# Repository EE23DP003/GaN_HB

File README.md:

# GaN_HB
Infineon GaN Half Bridge board design for validating PWM schemes using CHB grid connected inverter

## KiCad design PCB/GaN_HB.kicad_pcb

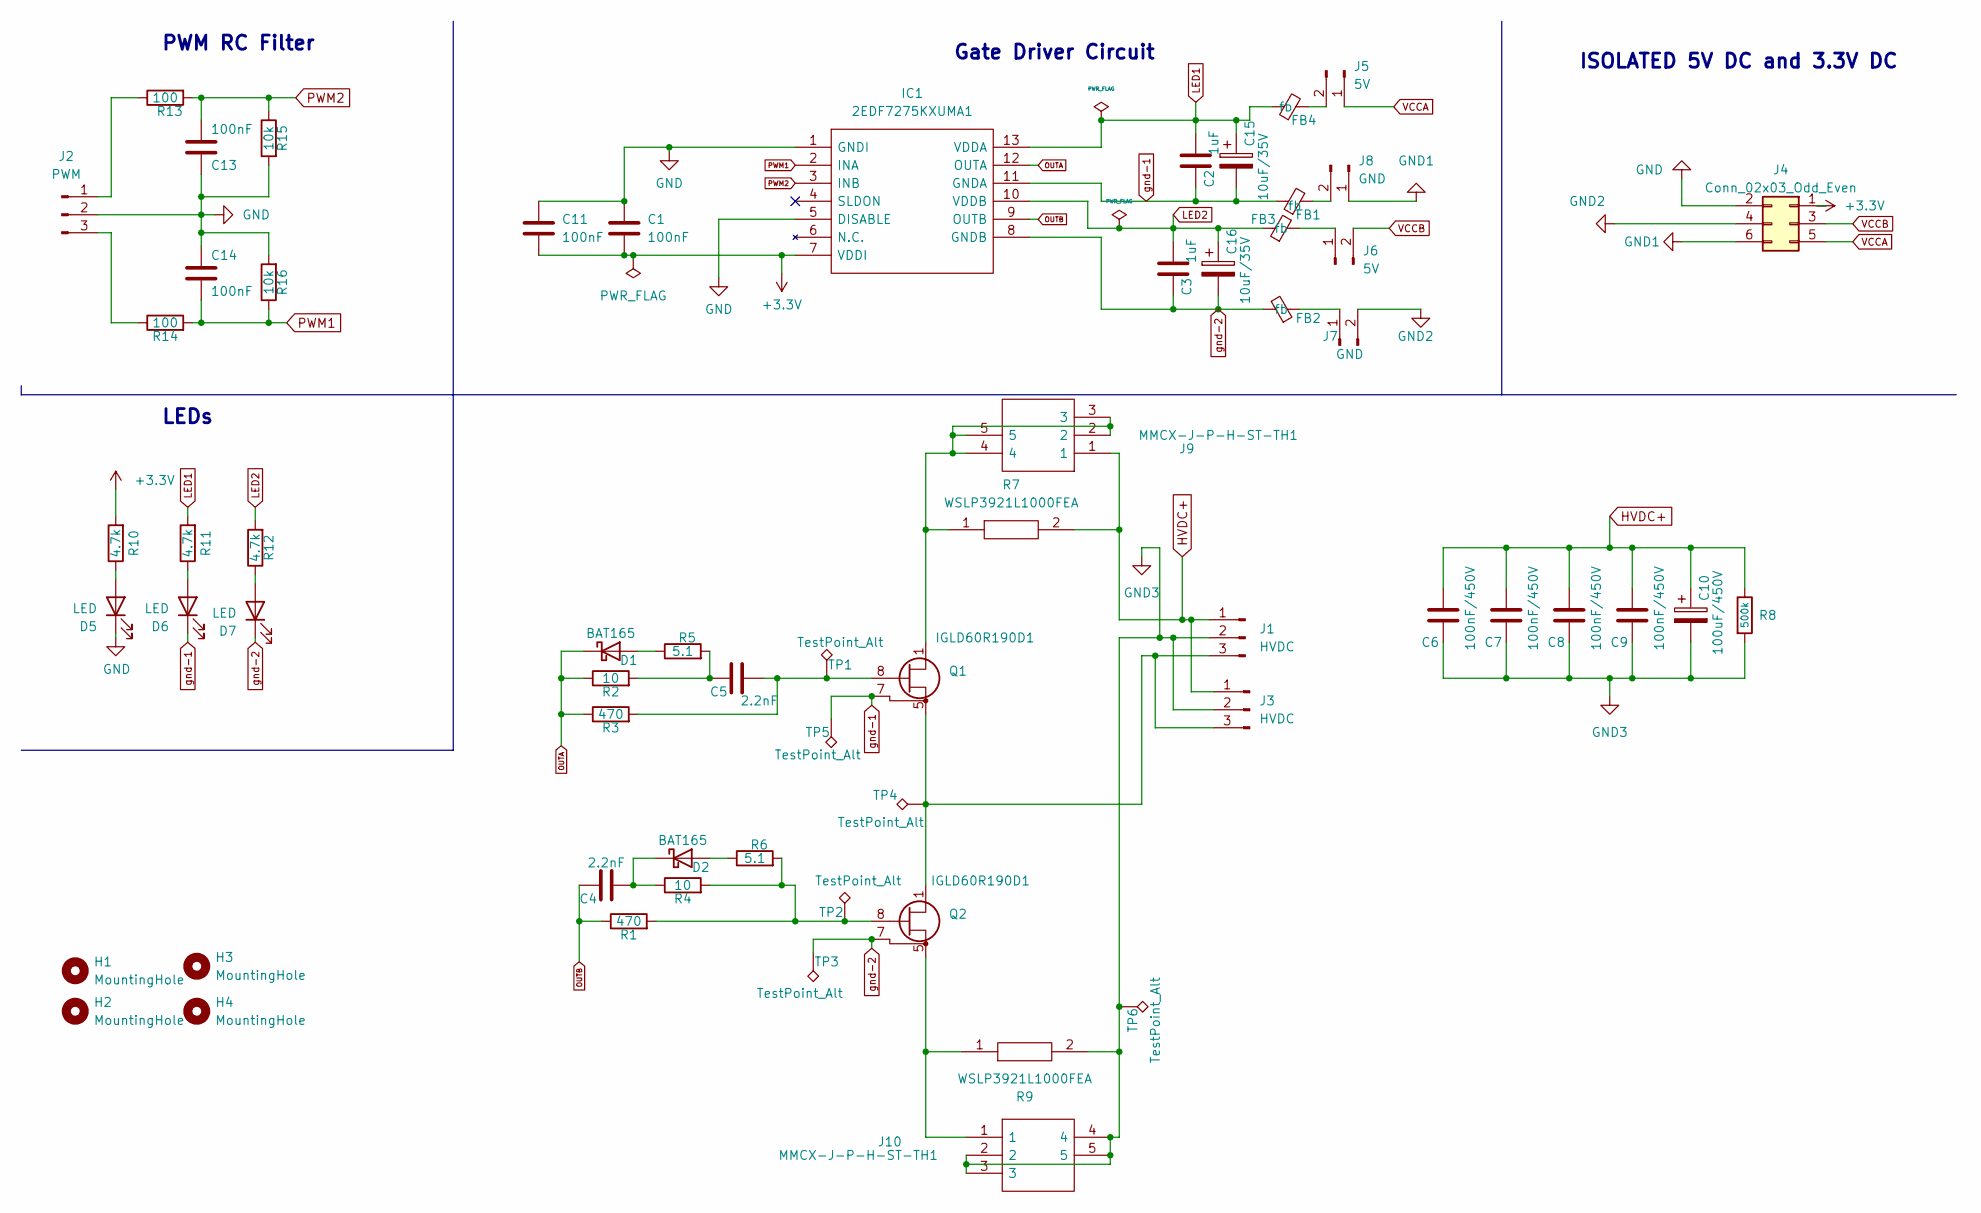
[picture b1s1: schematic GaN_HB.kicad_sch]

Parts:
C1, C11, C13, C14: 100nF; C_0805_2012Metric
C2, C3: 1uF; C_0805_2012Metric
C4, C5: 2.2nF; C_0805_2012Metric
C6, C7, C8, C9: 100nF/450V; C_1206_3216Metric
C10: 100uF/450V; CAPPRD750W80D1825H3200
C15, C16: 10uF/35V; CP_Elec_5x5.3
D1, D2: BAT165; D_SOD-323
D5, D6, D7: LED; LED_0805_2012Metric
FB1, FB2, FB3, FB4: fb; R_0805_2012Metric
H1, H2, H3, H4: MountingHole; MountingHole_3.2mm_M3
IC1: 2EDF7275KXUMA1; TFLGA65P500X500X106-14_13N-V; Mouser Part Number 726-2EDF7275KXUMA1
J1, J3: HVDC; Molex_KK-396_A-41791-0003_1x03_P3.96mm_Vertical
J2: PWM; Molex_KK-254_AE-6410-03A_1x03_P2.54mm_Vertical
J4: Conn_02x03_Odd_Even; PinSocket_2x03_P2.54mm_Horizontal
J5, J6: 5V; PinHeader_1x02_P2.54mm_Vertical
J7, J8: GND; PinHeader_1x02_P2.54mm_Vertical
J9, J10: MMCX-J-P-H-ST-TH1; MMCXJPHSTTH1; Mouser Part Number 200-MMCXJPHSTTH1
Q1, Q2: IGLD60R190D1; Infineon_PG-LSON-8-1
R1, R3: 470; R_0805_2012Metric
R2, R4: 10; R_0805_2012Metric
R5, R6: 5.1; R_0805_2012Metric
R7, R9: WSLP3921L1000FEA; RESC10052X50N; Manufacturer_Part_Number WSLP3921L1000FEA; Mouser Part Number 71-WSLP3921L1000FEA
R8: 500k; R_0805_2012Metric
R10, R11, R12: 4.7k; R_0805_2012Metric
R13, R14: 100; R_0805_2012Metric
R15, R16: 10k; R_0805_2012Metric
TP1, TP2, TP3, TP4, TP5, TP6: TestPoint_Alt; TestPoint_Keystone_5000-5004_Miniature

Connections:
+3.3V: C1.2, C11.2, IC1.7 (VDDI), J4.1, R10.2
GND: C1.1, C11.1, C13.1, C14.1, D5.1 (K), IC1.1 (GNDI), IC1.5 (DISABLE), J2.2, J4.2, R15.2, R16.2
GND1: J4.6, J8.1
GND2: J4.4, J7.2
GND3: C6.2, C7.2, C8.2, C9.2, C10.2, J1.2, J3.2, J10.2, J10.3, J10.4, J10.5, R8.2, R9.2, TP6.1
HVDC+: C6.1, C7.1, C8.1, C9.1, C10.1, J1.1, J3.1, J9.1, R7.2, R8.1
LED1: C2.2, C15.1, FB4.1, IC1.13 (VDDA), R11.2
LED2: C3.2, C16.1, FB3.1, IC1.10 (VDDB), R12.2
unnamed: C5.1, R2.2, R5.2
unnamed: D1.2 (A), R5.1
unnamed: D2.2 (A), R6.1
unnamed: C4.2, D2.1 (K), R4.1
unnamed: D5.2 (A), R10.1
unnamed: D6.2 (A), R11.1
unnamed: D7.2 (A), R12.1
unnamed: J1.3, J3.3, Q1.5 (S), Q1.6 (S), Q1.9 (S), Q2.1 (D), Q2.2 (D), Q2.3 (D), Q2.4 (D), TP4.1
unnamed: J2.1, R13.1
unnamed: J2.3, R14.1
unnamed: FB4.2, J5.2
unnamed: FB3.2, J6.1
unnamed: FB2.1, J7.1
unnamed: FB1.2, J8.2
unnamed: J9.2, J9.3, J9.4, J9.5, Q1.1 (D), Q1.2 (D), Q1.3 (D), Q1.4 (D), R7.1
unnamed: J10.1, Q2.5 (S), Q2.6 (S), Q2.9 (S), R9.1
unnamed: C5.2, Q1.8 (G), R3.2, TP1.1
unnamed: Q2.8 (G), R1.2, R4.2, R6.2, TP2.1
OUTA: D1.1 (K), IC1.12 (OUTA), R2.1, R3.1
OUTB: C4.1, IC1.9 (OUTB), R1.1
PWM1: C14.2, IC1.2 (INA), R14.2, R16.1
PWM2: C13.2, IC1.3 (INB), R13.2, R15.1
VCCA: J4.5, J5.1
VCCB: J4.3, J6.2
gnd-1: C2.1, C15.2, D6.1 (K), FB1.1, IC1.11 (GNDA), Q1.7 (SS), TP5.1
gnd-2: C3.1, C16.2, D7.1 (K), FB2.2, IC1.8 (GNDB), Q2.7 (SS), TP3.1

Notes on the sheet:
LEDs
ISOLATED 5V DC and 3.3V DC
PWM RC Filter
Gate Driver Circuit

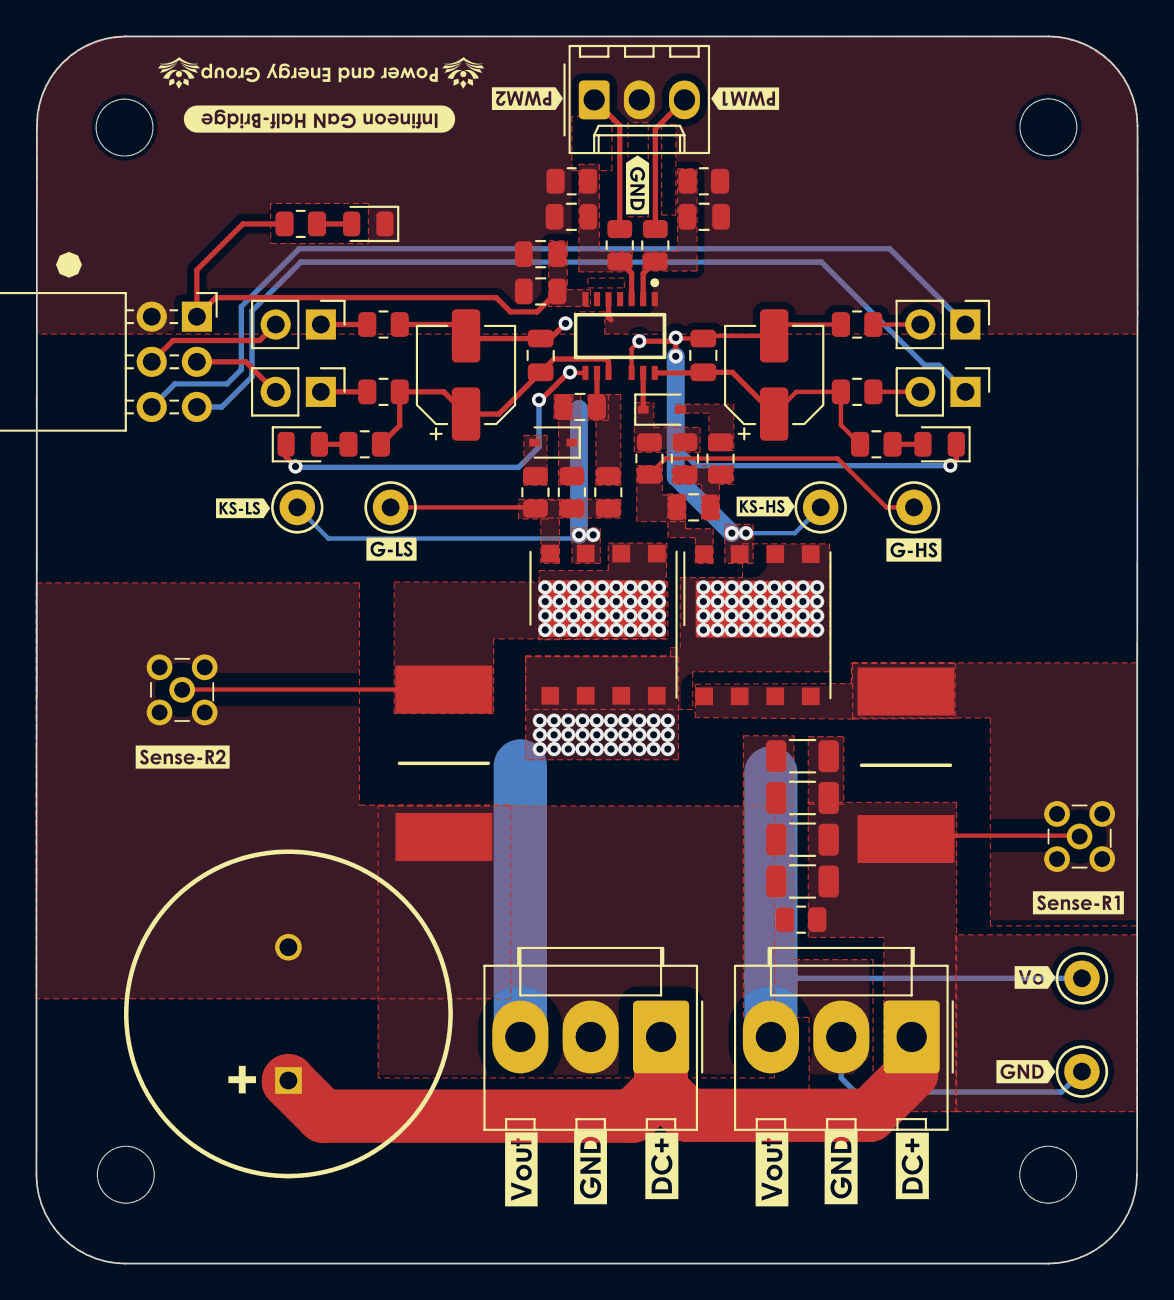
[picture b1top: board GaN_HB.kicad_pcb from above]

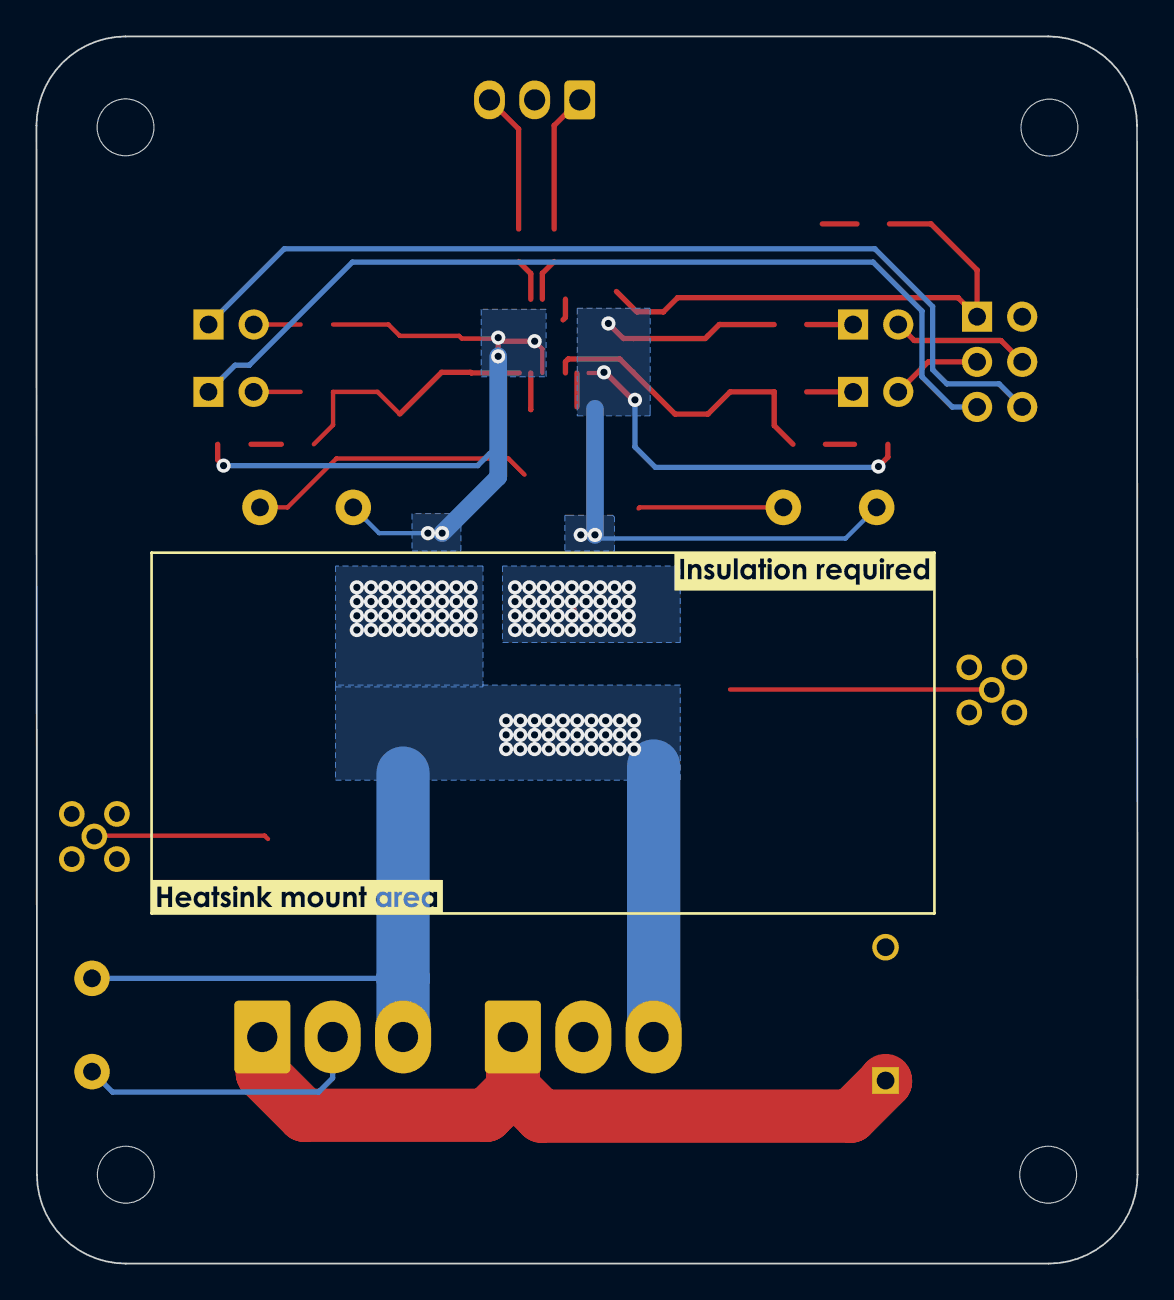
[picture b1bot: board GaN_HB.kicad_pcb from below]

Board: 2 copper layers, 62.0 x 69.1 mm, 86 parts (2 on the bottom side), 34 nets.

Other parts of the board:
kibuzzard-63EDD5C6: G***; kibuzzard-63EDD5C6
kibuzzard-63EDD5E0: G***; kibuzzard-63EDD5E0
kibuzzard-63EDD791: G***; kibuzzard-63EDD791
kibuzzard-63EDDA14: G***; kibuzzard-63EDDA14
kibuzzard-63EE9044, kibuzzard-63EE9044#2: G***; kibuzzard-63EE9044
kibuzzard-63EE9091, kibuzzard-63EE9091#2: G***; kibuzzard-63EE9091
kibuzzard-63FF1A06: G***; kibuzzard-63FF1A06
kibuzzard-63FF1A39: G***; kibuzzard-63FF1A39
kibuzzard-63FF2B27: G***; kibuzzard-63FF2B27
kibuzzard-63FF19DB: G***; kibuzzard-63FF19DB
kibuzzard-63FF19FC: G***; kibuzzard-63FF19FC
kibuzzard-63FF27E9: G***; kibuzzard-63FF27E9
kibuzzard-63FF2952: G***; kibuzzard-63FF2952
kibuzzard-640A1BB7: G***; kibuzzard-640A1BB7
kibuzzard-640A1BC5: G***; kibuzzard-640A1BC5
kibuzzard-640A14F1: G***; kibuzzard-640A14F1
kibuzzard-640A15A1: G***; kibuzzard-640A15A1
kibuzzard-640A15B0: G***; kibuzzard-640A15B0
kibuzzard-640A15B9: G***; kibuzzard-640A15B9
kibuzzard-640AA4D3: G***; kibuzzard-640AA4D3
kibuzzard-640AA404: G***; kibuzzard-640AA404

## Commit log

2025-10-06 updated design files
